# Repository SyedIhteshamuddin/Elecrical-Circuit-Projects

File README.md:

# Electrical Engineering Portfolio 

Welcome! This repository documents my hands-on engineering projects completed while exploring electronics, embedded systems, circuit design, and PCB development.

My goal is to build practical engineering skills through designing, simulating, documenting, and improving real hardware projects rather than only studying theory.

---

## Current Projects

### ATmega328P-Smart-Assistive-Navigator PCB
⭐ *Latest Project*

This project documents the complete design of a custom two-layer printed circuit board (PCB) for an ATmega328P-based assistive navigation hardware platform.

### SAN - (Smart Assistive Navigator)
An Arduino-based prototype that assists visually impaired users by detecting nearby obstacles and providing feedback using ultrasonic sensors and vibration/audio alerts.

### Adaptive Smart Light System
An automatic lighting system that adjusts LED brightness according to ambient light levels using an LDR sensor.

### Smart Gas Leakage System
A gas monitoring and alert system that detects gas levels and responds using LEDs, LCD messages, and a buzzer alarm.

More projects and experiments will be added over time as I continue learning.

---
## Skills Demonstrated

Throughout these projects, I have gained practical experience in:

### Electronics
- Circuit Analysis
- Embedded Systems
- Sensor Interfacing
- Hardware Documentation
- PCB Design
- KiCad
- Schematic Capture
- PCB Layout
- Component Placement
- Manual Routing
- DRC Verification
- Gerber Generation

### Programming
- Arduino
- Embedded C++
- Firmware Development

### Engineering Tools
- MATLAB
- Autodesk Tinkercad
- KiCad

---
## Project Files

Each project folder usually contains:

- `.ino` file → Arduino code for the project
- `.mp4` file → working demo/simulation video
- `.png` file → circuit design screenshot
- `bom.csv` → components used in the circuit
- `README.md` → explanation of how the project works

---
## Certificates & Learning

This repository also includes a few engineering-related certificates and learning records connected to:

- MITx Certificate
-Circuit Analysis
-Electronics

- MATLAB
-automation
-embedded systems
-engineering software/tools

- Altium PCB Design Course
 -PCB Designing
 -PCB Manufacturing
 -PCB Simulation

Check Certifications Folder for more details.
---

## Why I Started This Repository

I created this repository to document my progress while exploring electronics and embedded systems.

Right now I’m mainly focused on:
- sensor-based systems
- automation concepts
- Arduino projects
- circuit simulation
- learning how different components interact in a complete system

I’ll continue updating this repository as I build more projects and improve my understanding.

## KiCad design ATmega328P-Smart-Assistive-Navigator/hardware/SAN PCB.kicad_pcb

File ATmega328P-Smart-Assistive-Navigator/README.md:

# ATmega328P Smart Assistive Navigator PCB

</p>
Designed as a personal hardware engineering project to learn the complete PCB development workflow from schematic capture to fabrication-ready manufacturing files using KiCad.

---

# Project Overview

This project documents the complete design of a custom two-layer printed circuit board (PCB) for an ATmega328P-based assistive navigation hardware platform.

The primary objective was to gain practical experience with the complete PCB design workflow rather than relying on development boards such as the Arduino Uno. The design process included schematic capture, footprint assignment, PCB layout, routing, electrical verification, design rule checking (DRC), and fabrication file generation using KiCad.

Although the board has not been physically manufactured or tested, the project successfully demonstrates a complete PCB design workflow suitable for fabrication.

---

# Gallery

## Design Files

<table align="center">
<tr>
<td align="center" width="50%">

### Schematic

</td>

<td align="center" width="50%">

### PCB Layout

</td>
</tr>
</table>

---

## Final PCB

<table align="center">
<tr>

<td align="center" width="33%">

### Front View

</td>

<td align="center" width="33%">

### Back View

</td>

<td align="center" width="33%">

### Isometric View

</td>

</tr>
</table>

---

# Objectives

- Learn professional PCB design using KiCad
- Design a custom PCB around the ATmega328P microcontroller
- Understand schematic capture and PCB layout
- Learn component placement strategies
- Perform manual PCB routing
- Verify the design using Design Rule Checks (DRC)
- Generate fabrication-ready Gerber and drill files

---

# System Features

- ATmega328P microcontroller
- Dual HC-SR04 ultrasonic sensor interfaces
- I²C LCD display interface
- Piezo buzzer output
- PN2222A transistor-based vibration motor driver
- External 16 MHz crystal oscillator
- AVR ISP programming header
- Reset push button
- Decoupling capacitor
- Two-layer PCB layout

---

# Hardware Components

| Component | Purpose |
|------------|------------------------------|
| ATmega328P | Main microcontroller |
| HC-SR04 ×2 | Obstacle detection |
| 16 MHz Crystal | System clock |
| 22 pF Capacitors | Crystal load capacitors |
| 100 nF Capacitor | Power supply decoupling |
| PN2222A | Motor driver transistor |
| 1N4007 | Flyback protection diode |
| Piezo Buzzer | Audio feedback |
| I²C LCD Header | Display interface |
| AVR ISP Header | Programming interface |
| Push Button | Reset switch |

---

## PCB Specifications

| Parameter | Value |
|-----------|--------|
| PCB Software | KiCad 10 |
| Board Type | Custom PCB |
| PCB Layers | 2 |
| Routing | Manual |
| Mounting Style | Through-Hole (THT) |
| Microcontroller | ATmega328P-PU |
| Board Verification | Design Rule Check (DRC) Passed |
| Manufacturing Files | Gerber + Drill Files Generated |
| PCB Status | Fabrication-Ready Design |

Copper Thickness: 1 oz (standard fabrication assumption)

Minimum Trace Width:
0.25 mm

Minimum Clearance:
0.20 mm

## Design Workflow

This project followed a complete PCB development workflow:

1. Requirement definition
2. Schematic capture
3. Component footprint assignment
4. PCB floorplanning
5. Manual component placement
6. Manual two-layer routing
7. Design Rule Check (DRC)
8. Fabrication file generation
9. 3D verification
10. Documentation

---

## Design Validation

| Check | Status |
|---------|---------|
| Electrical Rule Check (ERC) | Completed |
| Design Rule Check (DRC) | Passed |
| PCB Routing | Completed |
| Gerber Files | Generated |
| Drill Files | Generated |
| Ready for Fabrication | Yes (Design Only) |
| Physical Assembly | Not Performed |

> **Note:** This project has not been physically manufactured or electrically validated. "Ready for Fabrication" indicates that the design files were successfully generated and verified using KiCad's design checks.

---
## Repository Structure
```text
ATmega328P-Smart-Assistive-Navigator-PCB
│
├── README.md
│
├── hardware
│   ├── SAN PCB.kicad_pcb
│   ├── SAN PCB.kicad_sch
│   └── SAN PCB.kicad_pro
│
├── firmware
│   └── SAN.ino
│
├── fabrication
│   ├── Fabrication_Files.zip
│   └── README.md
│
├── bom
│   └── BOM.csv
│
├── docs
│   ├── SAN PCB.pdf
│   └── SAN PCB PrintView.pdf
│
└── images
    ├── schematic.png
    ├── pcb_layout.png
    ├── pcb_front.png
    ├── pcb_back.png
    └── pcb_isometric.png
```

---

# Challenges Faced

During the development of this project I encountered several practical PCB design challenges including:

- Selecting appropriate footprints
- Crystal oscillator placement
- Decoupling capacitor positioning
- PCB routing optimization
- Managing trace intersections
- Using both copper layers effectively
- Resolving Design Rule Check (DRC) violations
- Preparing fabrication outputs

Working through these issues provided valuable hands-on experience with the PCB design process.

---
## Design Decisions

Several design decisions were made during the PCB layout to improve reliability and follow standard PCB design practices.

- Placed the 100 nF decoupling capacitor close to the ATmega328P power pins to reduce supply noise.
- Positioned the 16 MHz crystal oscillator adjacent to the microcontroller to minimize clock trace length.
- Used dedicated 22 pF load capacitors for crystal stability.
- Included an ISP programming header for firmware uploading and debugging.
- Used a PN2222A transistor to safely drive the vibration motor from the microcontroller.
- Added a flyback diode (1N4007) across the motor output to protect the transistor from inductive voltage spikes.
- Routed signal traces manually to reduce unnecessary crossings and improve readability.
- Performed Design Rule Checks (DRC) before generating fabrication files.
  
---

# Lessons Learned

Through this project I developed practical experience with:

- PCB schematic design
- Component footprint selection
- Two-layer PCB layout
- Manual routing techniques
- PCB design constraints
- Design verification
- Manufacturing file generation
- Professional engineering documentation
- Tradeoffs between routing simplicity and board compactness
- Importance of component placement before routing

---
## Skills Demonstrated

Through this project I gained practical experience in:

- PCB Design using KiCad
- Electronic Schematic Capture
- Footprint Selection
- Component Placement
- Manual PCB Routing
- Two-Layer PCB Design
- Design Rule Verification (DRC)
- Gerber File Generation
- Bill of Materials (BOM) Creation
- Hardware Documentation
- Basic Embedded Hardware Design
-  PCB Manufacturing Documentation
---

# Future Improvements

Future versions of this project could include:

- Physical PCB fabrication
- Hardware assembly and testing
- USB programming interface
- Improved component placement
- Reduced PCB dimensions
- Surface-mount (SMD) version
- Power supply optimization

---

# Author

**[Syed Ihteshamuddin]**

High School Student | Aspiring Electrical Engineer

Areas of Interest:

- Electrical Engineering
- Embedded Systems
- PCB Design
- Hardware Development

GitHub: https://github.com/syedihteshamuddin

---

> This repository documents a personal learning project completed to develop practical skills in embedded hardware and PCB design.

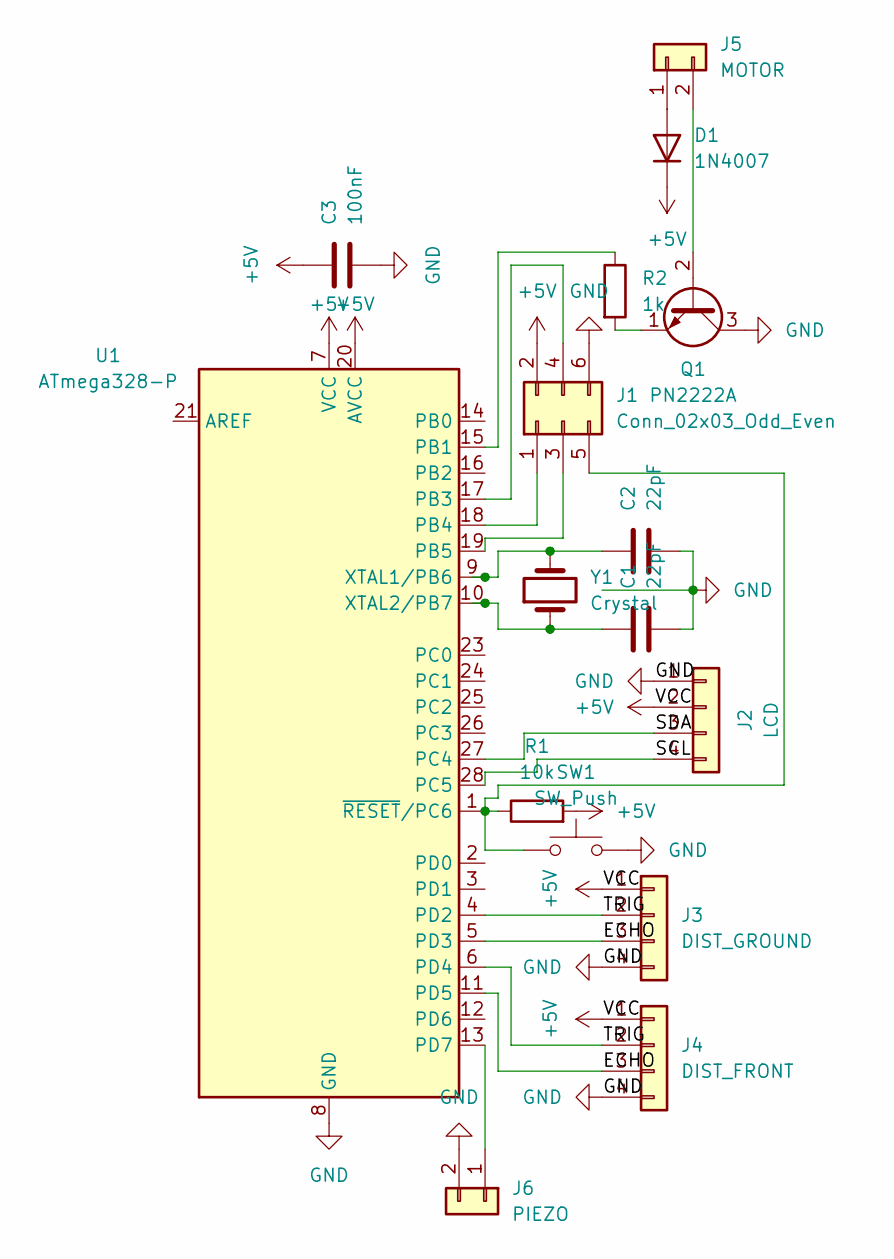
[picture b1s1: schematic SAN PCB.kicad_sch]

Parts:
C1, C2: 22pF; C_0805_2012Metric
C3: 100nF; C_0805_2012Metric
D1: 1N4007; D_DO-41_SOD81_P10.16mm_Horizontal
J1: Conn_02x03_Odd_Even; PinHeader_2x03_P2.54mm_Vertical
J2: LCD; PinHeader_1x04_P2.54mm_Vertical
J3: DIST_GROUND; PinHeader_1x04_P2.54mm_Vertical
J4: DIST_FRONT; PinHeader_1x04_P2.54mm_Vertical
J5: MOTOR; PinHeader_1x02_P2.54mm_Vertical
J6: PIEZO; PinHeader_1x02_P2.54mm_Vertical
Q1: PN2222A; TO-92_Inline
R1: 10k; R_Axial_DIN0207_L6.3mm_D2.5mm_P7.62mm_Horizontal
R2: 1k; R_Axial_DIN0207_L6.3mm_D2.5mm_P7.62mm_Horizontal
SW1: SW_Push; SW_PUSH_6mm
U1: ATmega328-P; DIP-28_W7.62mm
Y1: Crystal; Crystal_HC49-U_Vertical

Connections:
+5V: C3.1, D1.1 (K), J1.2, J2.2 (VCC), J3.1, J4.1, R1.2, U1.7 (VCC), U1.20 (AVCC)
/ECHO: J3.3, J4.3, U1.5 (PD3), U1.11 (PD5)
/SCL: J2.4 (SCL), U1.28 (PC5)
/SDA: J2.3 (SDA), U1.27 (PC4)
/TRIG: J3.2, J4.2, U1.4 (PD2), U1.6 (PD4)
GND: C1.2, C2.2, C3.2, J1.6, J2.1 (GND), J3.4, J4.4, J6.2, Q1.3 (C), SW1.2, U1.8 (GND), U1.22 (GND)
unnamed: D1.2 (A), J5.1
unnamed: J1.1, U1.18 (PB4)
unnamed: J1.3, U1.19 (PB5)
unnamed: J1.4, U1.17 (PB3)
unnamed: J1.5, R1.1, SW1.1, U1.1 (~RESET/PC6)
unnamed: J5.2, Q1.2 (B)
unnamed: J6.1, U1.13 (PD7)
unnamed: Q1.1 (E), R2.2
unnamed: R2.1, U1.15 (PB1)
unnamed: C2.1, U1.9 (XTAL1/PB6), Y1.2
unnamed: C1.1, U1.10 (XTAL2/PB7), Y1.1

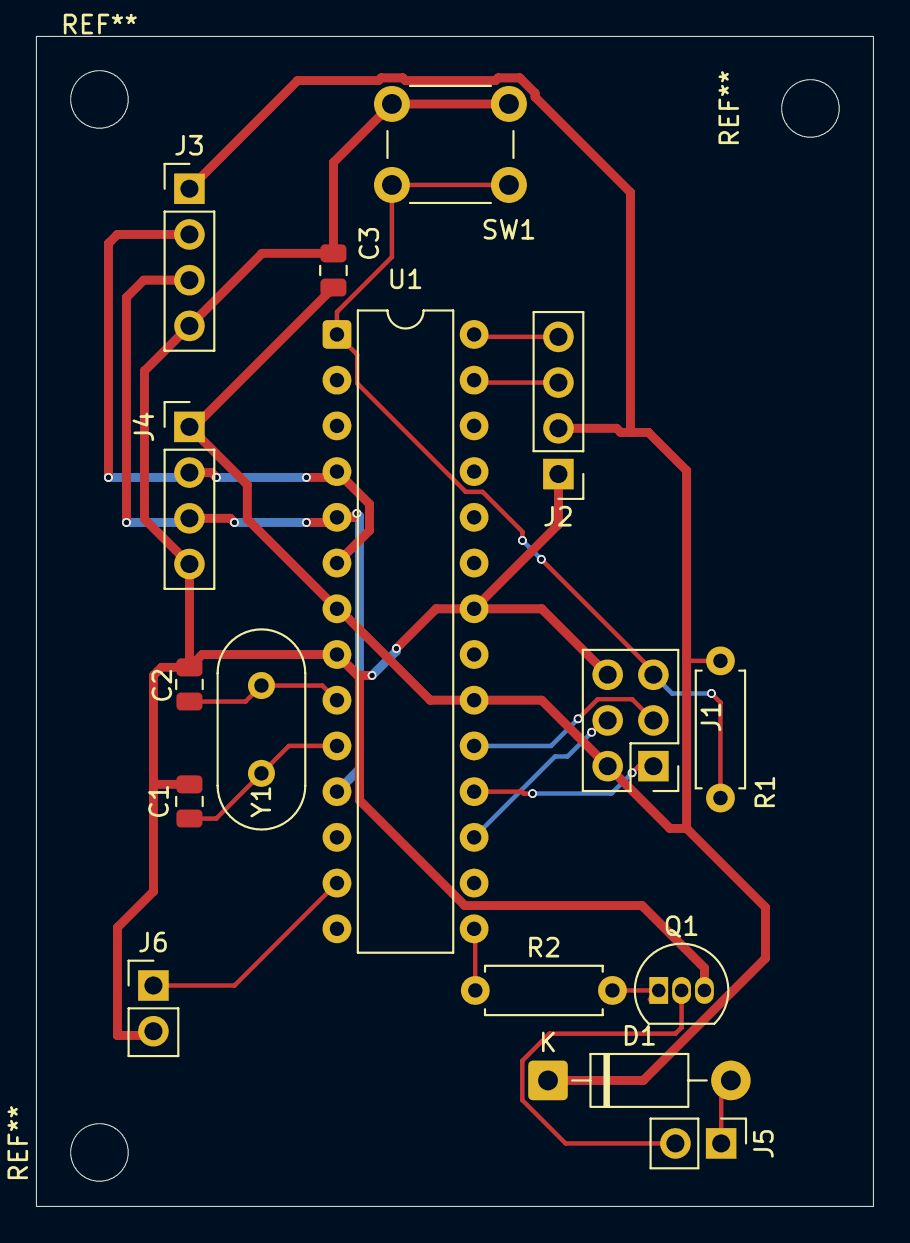
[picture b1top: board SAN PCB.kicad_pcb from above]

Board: 2 copper layers, 46.5 x 65.0 mm, 16 parts (0 on the bottom side), 17 nets.

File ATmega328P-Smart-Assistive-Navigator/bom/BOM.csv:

Item,Reference,Quantity,Component,Value/Part Number,Package,Description
1,U1,1,Microcontroller,ATmega328P-PU,DIP-28,8-bit AVR microcontroller
2,Y1,1,Crystal,16 MHz,HC-49S,Clock source for ATmega328P
3,C1,1,Ceramic Capacitor,22 pF,Radial THT,Crystal load capacitor
4,C2,1,Ceramic Capacitor,22 pF,Radial THT,Crystal load capacitor
5,C3,1,Ceramic Capacitor,100 nF,Radial THT,Power supply decoupling capacitor
6,R1,1,Resistor,10 kΩ,Axial THT,ATmega328P reset pull-up resistor
7,R2,1,Resistor,1 kΩ,Axial THT,Base current limiting resistor for transistor
8,Q1,1,NPN Transistor,PN2222A,TO-92,Motor driver transistor
9,D1,1,Diode,1N4007,DO-41,Flyback protection diode
10,SW1,1,Tactile Push Button,6x6 mm,THT,Reset push button
11,J1,1,AVR ISP Header,2x3 Pin,THT,ISP programming connector
12,J2,1,LCD Header,1x4 Pin,THT,I2C LCD interface header
13,J3,1,Sensor Header,1x4 Pin,THT,Ground ultrasonic sensor connector
14,J4,1,Sensor Header,1x4 Pin,THT,Front ultrasonic sensor connector
15,J5,1,Motor Connector,1x2 Pin,THT,Motor output connector
16,J6,1,Piezo Connector,1x2 Pin,THT,Piezo buzzer connector

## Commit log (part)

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2026-05-13 Rename .brd to Adaptive Smart Street Light System.brd
2026-05-16 Create FOLDER
